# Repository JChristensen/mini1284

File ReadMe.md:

# The Mighty Mini 1284P v1.1#

A minimal breadboard-friendly design for the ATmega1284P MCU, named after [maniacbug's "mighty-1284p" Arduino core](http://goo.gl/iBJMnJ), in recognition of his contribution to the Arduino community. It has all necessary support components, ICSP and FTDI headers, and all GPIO pins are brought out to headers.

v1.1 differs from v1.0 only in that a different crystal and different value loading capacitors are used.

05May2014 - An updated version of maniacbug's mighty-1284p core based on Arduino 1.0.5 is available [here](http://goo.gl/l7cPbX).

Printed circuit boards can be [ordered through OSH Park](http://goo.gl/QvPN2v).

A bill of materials is [available on Mouser](http://goo.gl/KgAAyT).

I'd be interested to hear from anyone that builds one.

#### CC BY-SA ####
"The Mighty Mini 1284P" by Jack Christensen is licensed under [CC BY-SA 4.0](http://creativecommons.org/licenses/by-sa/4.0/).

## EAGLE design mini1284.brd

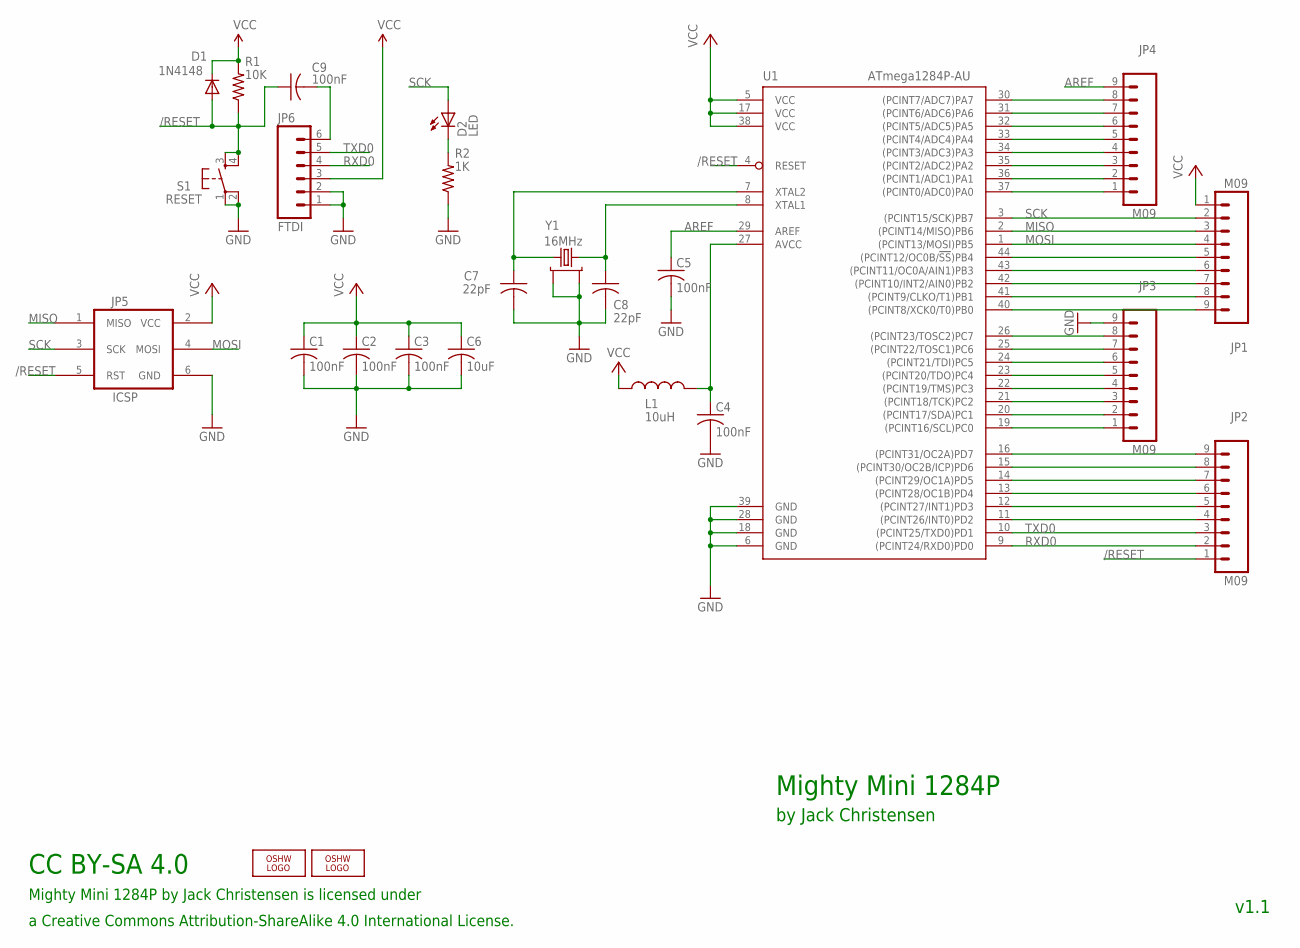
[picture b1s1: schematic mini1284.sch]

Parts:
C1, C2, C3, C4, C5, C9: 100nF; M0805
C6: 10uF; M1206
C7, C8: 22pF; M0805
D1: 1N4148; SOD-323F-A
D2: LED; D0805A
JP1, JP2, JP3, JP4: M09; 1X09
JP5: ICSP; 2X3_LOCK
JP6: FTDI; 1X06_LOCK
L1: 10uH; M0805
LOGO1: OSHW_LOGO_8MILX0150-NT; OSHW_8X150_NOTEXT
LOGO2: OSHW_LOGO_6MILX0100-NT; OSHW_6X100_NOTEXT
R1: 10K; M0805
R2: 1K; M0805
S1: RESET; PTS810
U1: ATmega1284P-AU; TQFP44
Y1: 16MHz; CRYSTAL-EPSON-TSX3225

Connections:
/RESET: C9.1, D1.A, JP2.1, JP5.5 (RST), R1.1, S1.3 (S), S1.4 (S1), U1.4 (RESET)
AREF: C5.1, JP4.9, U1.29 (AREF)
GND: C1.2, C2.2, C3.2, C4.2, C5.2, C6.2, C7.2, C8.2, JP3.9, JP5.6 (GND), JP6.1, JP6.2, R2.1, S1.1, S1.2 (P1), U1.6 (GND), U1.18 (GND), U1.28 (GND), U1.39 (GND), Y1.2, Y1.4
MISO: JP1.3, JP5.1 (MISO), U1.2 ((PCINT14/MISO)PB6)
MOSI: JP1.4, JP5.4 (MOSI), U1.1 ((PCINT13/MOSI)PB5)
unnamed: C4.1, L1.2, U1.27 (AVCC)
unnamed: C8.1, U1.8 (XTAL1), Y1.3
unnamed: C7.1, U1.7 (XTAL2), Y1.1
unnamed: JP2.4, U1.11 ((PCINT26/INT0)PD2)
unnamed: JP1.5, U1.44 ((PCINT12/OC0B/!SS!)PB4)
unnamed: JP1.6, U1.43 ((PCINT11/OC0A/AIN1)PB3)
unnamed: JP1.7, U1.42 ((PCINT10/INT2/AIN0)PB2)
unnamed: JP1.8, U1.41 ((PCINT9/CLKO/T1)PB1)
unnamed: JP1.9, U1.40 ((PCINT8/XCK0/T0)PB0)
unnamed: JP2.5, U1.12 ((PCINT27/INT1)PD3)
unnamed: JP2.6, U1.13 ((PCINT28/OC1B)PD4)
unnamed: JP2.7, U1.14 ((PCINT29/OC1A)PD5)
unnamed: JP2.8, U1.15 ((PCINT30/OC2B/ICP)PD6)
unnamed: JP2.9, U1.16 ((PCINT31/OC2A)PD7)
unnamed: JP3.1, U1.19 ((PCINT16/SCL)PC0)
unnamed: JP3.2, U1.20 ((PCINT17/SDA)PC1)
unnamed: JP3.3, U1.21 ((PCINT18/TCK)PC2)
unnamed: JP3.4, U1.22 ((PCINT19/TMS)PC3)
unnamed: JP3.5, U1.23 ((PCINT20/TDO)PC4)
unnamed: JP3.6, U1.24 ((PCINT21/TDI)PC5)
unnamed: JP3.7, U1.25 ((PCINT22/TOSC1)PC6)
unnamed: JP3.8, U1.26 ((PCINT23/TOSC2)PC7)
unnamed: JP4.1, U1.37 ((PCINT0/ADC0)PA0)
unnamed: JP4.2, U1.36 ((PCINT1/ADC1)PA1)
unnamed: JP4.3, U1.35 ((PCINT2/ADC2)PA2)
unnamed: JP4.4, U1.34 ((PCINT3/ADC3)PA3)
unnamed: JP4.5, U1.33 ((PCINT4/ADC4)PA4)
unnamed: JP4.6, U1.32 ((PCINT5/ADC5)PA5)
unnamed: JP4.7, U1.31 ((PCINT6/ADC6)PA6)
unnamed: JP4.8, U1.30 ((PCINT7/ADC7)PA7)
unnamed: D2.K (C), R2.2
RST: C9.2, JP6.6
RXD0: JP2.2, JP6.4, U1.9 ((PCINT24/RXD0)PD0)
SCK: D2.A, JP1.2, JP5.3 (SCK), U1.3 ((PCINT15/SCK)PB7)
TXD0: JP2.3, JP6.5, U1.10 ((PCINT25/TXD0)PD1)
VCC: C1.1, C2.1, C3.1, C6.1, D1.K, JP1.1, JP5.2 (VCC), JP6.3, L1.1, R1.2, U1.5 (VCC), U1.17 (VCC), U1.38 (VCC)

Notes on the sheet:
Mighty Mini 1284P
by Jack Christensen
v1.1
Mighty Mini 1284P by Jack Christensen is licensed under
CC BY-SA 4.0
a Creative Commons Attribution-ShareAlike 4.0 International License.

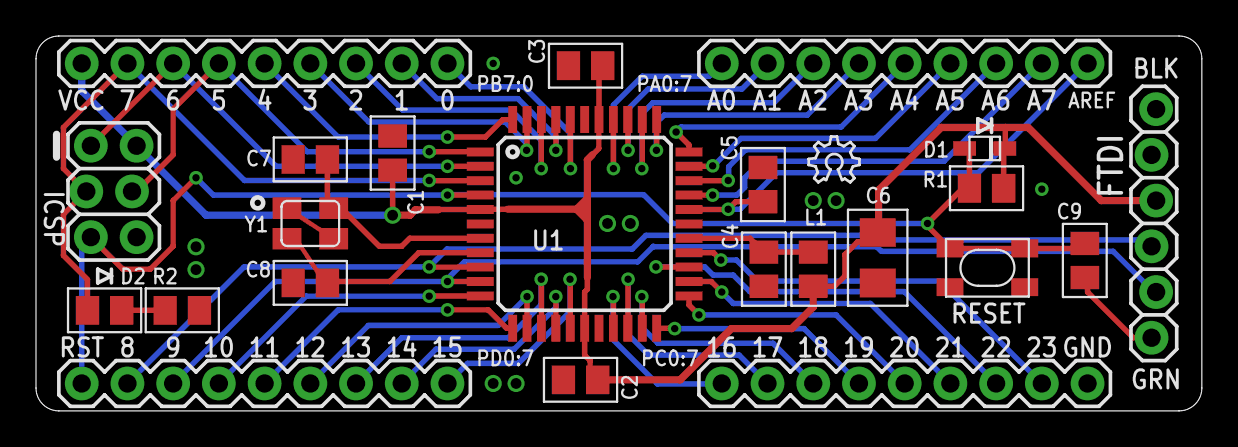
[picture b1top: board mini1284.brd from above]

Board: 2 copper layers, 64.8 x 20.8 mm, 25 parts (1 on the bottom side), 41 nets.

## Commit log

2014-04-07 Initial commit, before moving MCU.
2014-04-08 Routing looking pretty good.
2014-04-09 Routing refinements.
2014-04-09 Further tweaks.
2014-04-09 First run sent to fab.
2014-04-09 Change to Epson crystal.
2014-04-12 Minor text tweak.
2014-04-12 Minor tweaks.
2014-04-21 Silkscreen cosmetic changes.
2014-04-22 Add ReadMe and License files.
2014-05-14 Update ReadMe file, add photo.
2014-05-15 Update ReadMe file, add LICENSE file and photo.
2014-05-17 Update ReadMe file.

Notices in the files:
parts and their libraries:
SparkFun: Licensing: CC v3.0 Share-Alike You are welcome to use this library for commercial purposes.
